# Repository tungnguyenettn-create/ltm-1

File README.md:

# ltm-1

Mạch cảm biến chạm sử dụng TTP223

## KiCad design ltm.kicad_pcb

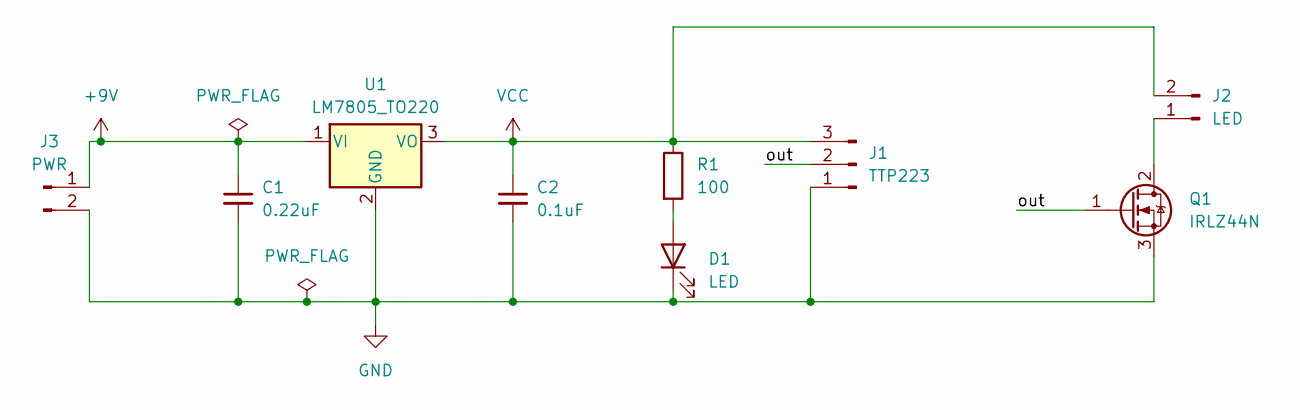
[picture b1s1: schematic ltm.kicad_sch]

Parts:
C1: 0.22uF; C_Radial_D4.0mm_H7.0mm_P1.50mm
C2: 0.1uF; C_Radial_D4.0mm_H7.0mm_P1.50mm
D1: LED; R_Axial_DIN0204_L3.6mm_D1.6mm_P5.08mm_Horizontal
J1: TTP223; PinHeader_1x03_P2.54mm_Vertical
J2: LED; PinHeader_1x02_P2.54mm_Vertical
J3: PWR; PinHeader_1x02_P2.54mm_Vertical
Q1: IRLZ44N; TO-220-3_Vertical
R1: 100; R_Axial_DIN0204_L3.6mm_D1.6mm_P5.08mm_Horizontal
U1: LM7805_TO220; TO-220-3_Vertical

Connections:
+9V: C1.1, J3.1, U1.1 (VI)
/out: J1.2, Q1.1 (G)
GND: C1.2, C2.2, D1.1 (K), J1.1, J3.2, Q1.3 (S), U1.2 (GND)
unnamed: D1.2 (A), R1.2
unnamed: J2.1, Q1.2 (D)
VCC: C2.1, J1.3, J2.2, R1.1, U1.3 (VO)

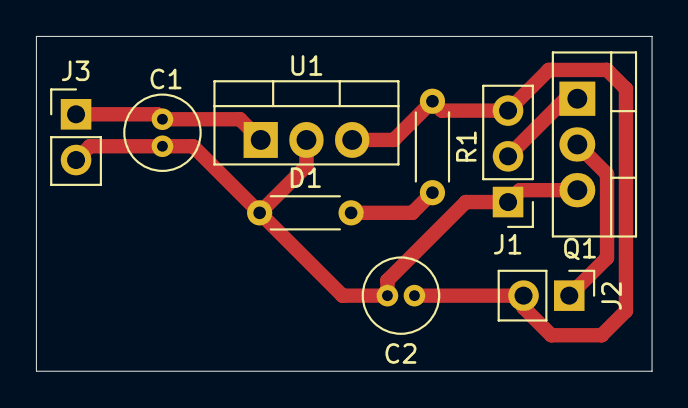
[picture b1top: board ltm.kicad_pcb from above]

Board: 2 copper layers, 34.2 x 18.6 mm, 9 parts (0 on the bottom side), 6 nets.
